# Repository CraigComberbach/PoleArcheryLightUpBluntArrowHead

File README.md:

View this project on [CADLAB.io](https://cadlab.io/project/29547). 

# Light up arrow tip
 
Used for pole archery at night using blunt arrows

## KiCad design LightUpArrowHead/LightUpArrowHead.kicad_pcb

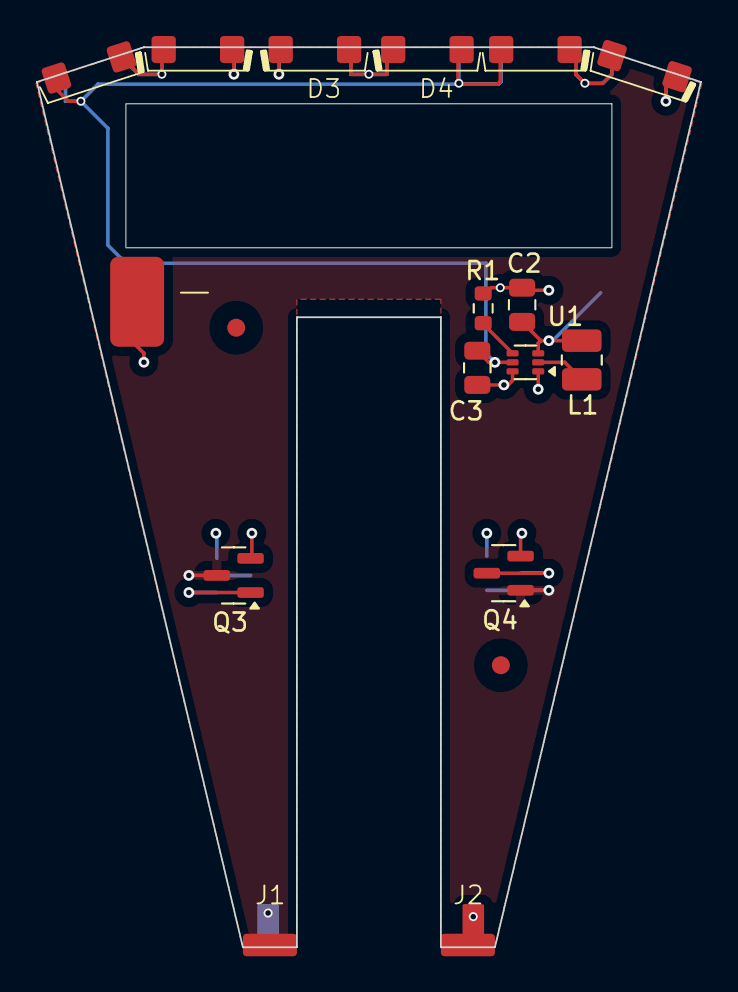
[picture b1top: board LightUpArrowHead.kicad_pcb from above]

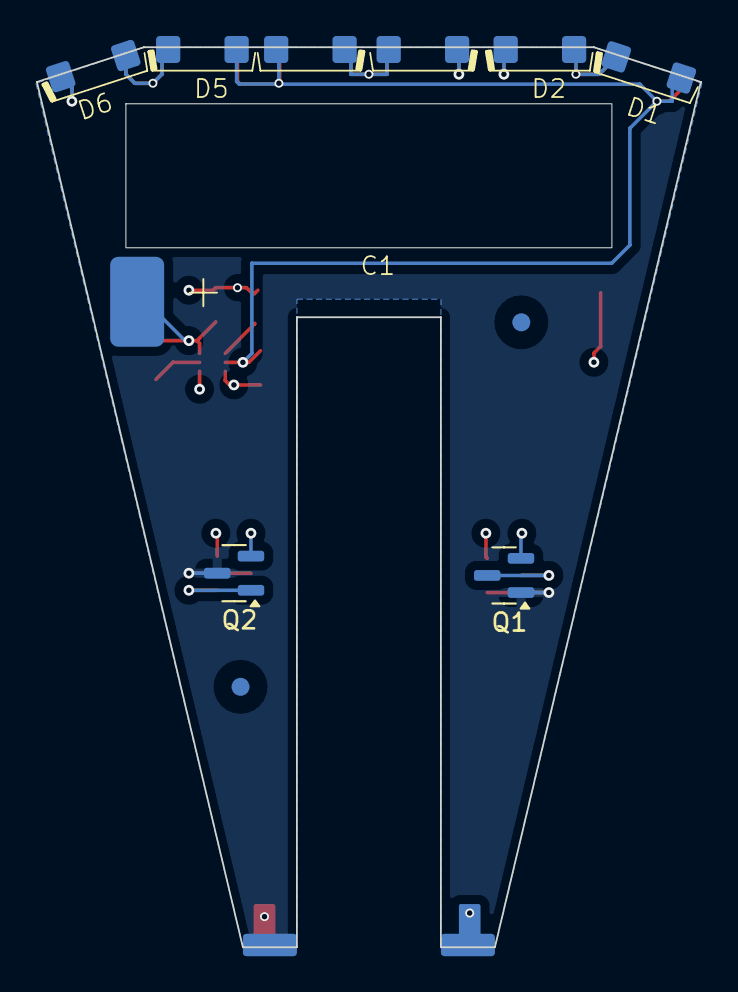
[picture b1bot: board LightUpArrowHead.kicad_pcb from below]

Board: 4 copper layers, 36.9 x 50.0 mm, 22 parts (9 on the bottom side), 10 nets.

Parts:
C1: Capacitor EDLC 5F 5.5V Diameter=26mm Height=7mm A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; Capacitor EDLC CDA CE Series H-Type Edge Mount
C2, C3: Capacitor Ceramic 10uF 16V X5R 0805; Capacitor 0805 (Metric 2012)
D1, D2, D3, D4, D5, D6: LED; Vishay VLD.1232G Family LED - Right Angle Edge Mount (Non-S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
FID1, FID2, FID3, FID4: Fiducial 1mm by 3mm
J1, J2: Edge Connector; Edge Plating 3mm
L1: Inductor 1uH; L_1008_2520Metric
Q1, Q2: DMP3099L; SOT-23
Q3, Q4: MOSFET N-Channel 30V 3.6A SOT-23-3; SOT-23
R1: r=3.01k; Resistor 0603 (Metric 1608)
U1: SOT-563

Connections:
/0.5-5V: C1.1, C2.1, L1.1, Q1.2 (S), Q2.2 (S), U1.1 (VIN), U1.3 (EN)
/5.5V: C3.1, D1.2 (A), D4.2 (A), D5.2 (A), U1.5 (VOUT)
/Vin+: J1.1, Q1.3 (D), Q2.1 (G), Q3.3 (D), Q4.1 (G)
/Vin-: J2.1, Q1.1 (G), Q2.3 (D), Q3.1 (G), Q4.3 (D)
GND: C1.2, C2.2, C3.2, D2.1 (K), D3.1 (K), D6.1 (K), Q3.2 (S), Q4.2 (S), R1.2, U1.6 (GND)
unnamed: D1.1 (K), D2.2 (A)
unnamed: D3.2 (A), D4.1 (K)
unnamed: D5.1 (K), D6.2 (A)
unnamed: L1.2, U1.2 (SW)
unnamed: R1.1, U1.4 (VSEL)

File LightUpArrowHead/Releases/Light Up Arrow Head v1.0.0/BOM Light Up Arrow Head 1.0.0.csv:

Reference,Value,Qty,MPN,Manufacturer,Technology
C1,Capacitor EDLC 5F 5.5V Diameter=26mm Height=7mm Axial Can THT,1,CE5R5505HF-ZJ,CDA (Zhifengwei Technology),Handplace
"D1,D2,D3,D4,D5,D6",LED Green (525nm) 2.9V 20mA 16000mcd SMD-2,6,VLDTG1232G-08,Vishay,Handplace
"Q3,Q4",MOSFET N-Channel 30V 3.6A SOT-23-3,2,DMG3406L,Diodes,SMT
"Q1,Q2",DMP3099L,2,DMP3099L,Diodes,SMT
L1,Inductor 1uH 3.3A 1008,1,WIP252012S-1R0MLDG,INPAQ Technology,SMT
"C2,C3",Capacitor Ceramic 10uF 16V X5R 0805,2,CL21A106KOQNNNG,Samsung Electro-Mechanics,SMT
R1,Resistor 3.01k 0603 1%,1,RMCF0603FT3K01,Stack Pole,SMT
U1,Regulator SMPS Boost Vin=0.5-5.5V Vout=1.8-5.5V 3MHz,1,TPS61299-Q1,Texas Instruments,SMT

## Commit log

2025-05-03 Schematic nearly complete
2025-06-16 PCB nearly complete
2025-07-07 Ready to order
2025-07-19 Ready for ordering
2025-09-01 Backlink to CADLAB.io has been added.
